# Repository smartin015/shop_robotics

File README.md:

# L2 Workshop Robotics

Firmware and control software for workshop/makerspace robots.

Ensembles of programs are started via the `./launch.sh` script.

# Layout

https://docs.google.com/drawings/d/1Mtd4x5n-zbuuM7uRhCHO-HnwOfN_e4qv0sVR_wNz95c

## Docs

Contains various docs / presentation elements

## Sim

Contains configuration and setup for physical simulation of hardware (typically using Webots).

This is sometimes paired up to real firmware/control software for integration testing.

## Hardware

Contains KiCAD, FreeCAD, SVG and other files for making the physical bits of robots.

## Firmware

Contains code that goes on the robot itself - firmware uses https://platformio.org/ as an environment to allow
for cross-platform builds and native emulation.

## Control

Contains higher-level control software that receives input from the user/environment and sends commands to the firmware.

## Display

Contains programs for displaying the state of the robot and what it sees - on a computer or on embedded screens

# Development

To setup a dev environment, you will need:

* [Docker](https://docs.docker.com/engine/install/ubuntu/)
  * IMPORTANT: [BuildKit](https://docs.docker.com/develop/develop-images/build_enhancements/) must be enabled for simulation builds
* [docker-compose](https://docs.docker.com/compose/install/)
* [This repository](https://github.com/smartin015/shop_robotics)

## Building containers

For the simulation container, you will need to enable BuildKit for docker (see above). You can ignore the warnings about missing environment variables, as they aren't used at build time.

```shell
docker-compose --profile headless --profile webots build
```

For manual/test image builds of the sim container, with more logs:
```
docker buildx build --progress=plain --tag shop_robotics_sim .
```

## Running profiles

```shell
docker-compose --env-file tribot.env -p shop_robotics --profile <webots|gamepad|headless> up
```

**Webots**

This runs a webots simulation of the AR3 robotic arm, with a separate web interface (localhost:8000) and a simulated copy of the firmware which normally lives in the control board of the robot.

Note that with `--stream` supplied in the `webots_sim` container command, you can visit `http://ip:1234/index.html` to see the [streaming server](https://cyberbotics.com/doc/guide/web-streaming) view of the robot simulation.

**Headless**

This runs a "stub" simulator (vastly simplified vs Webots) plus the firmware and web interface. Use this to prototype quickly on the web interface / firmware without having to restart Webots every time.

The `tribot_headless` version runs a 3-joint simulation, to match the omniwheel robot's number of wheels.

**Gamepad**

This runs an additional process that connects to a USB XBox 360 controller and allows for jogging the robot. It's currently hardcoded for 3 axes only,
and must be run along with another environment (e.g. `docker-compose --profile headless --profile gamepad up`)

# Extras

Possibly useful for getting MoveIt! control working: 

- (ROS) https://github.com/ongdexter/ar3_core
- (ROS2) https://github.com/RIF-Robotics/ar3_ros

# Lessons learned

* ZeroMQ: IPC can handle PAIR sockets, but:
  * If multiple users (i.e. firmware & sim containers, since firmware runs as a user and not root) the file must have the correct unix permissions (chmod 777 to be lazy)
  * Socket must remain open on both ends. When it closes, it can't be reopened. This is a property of PAIR sockets.

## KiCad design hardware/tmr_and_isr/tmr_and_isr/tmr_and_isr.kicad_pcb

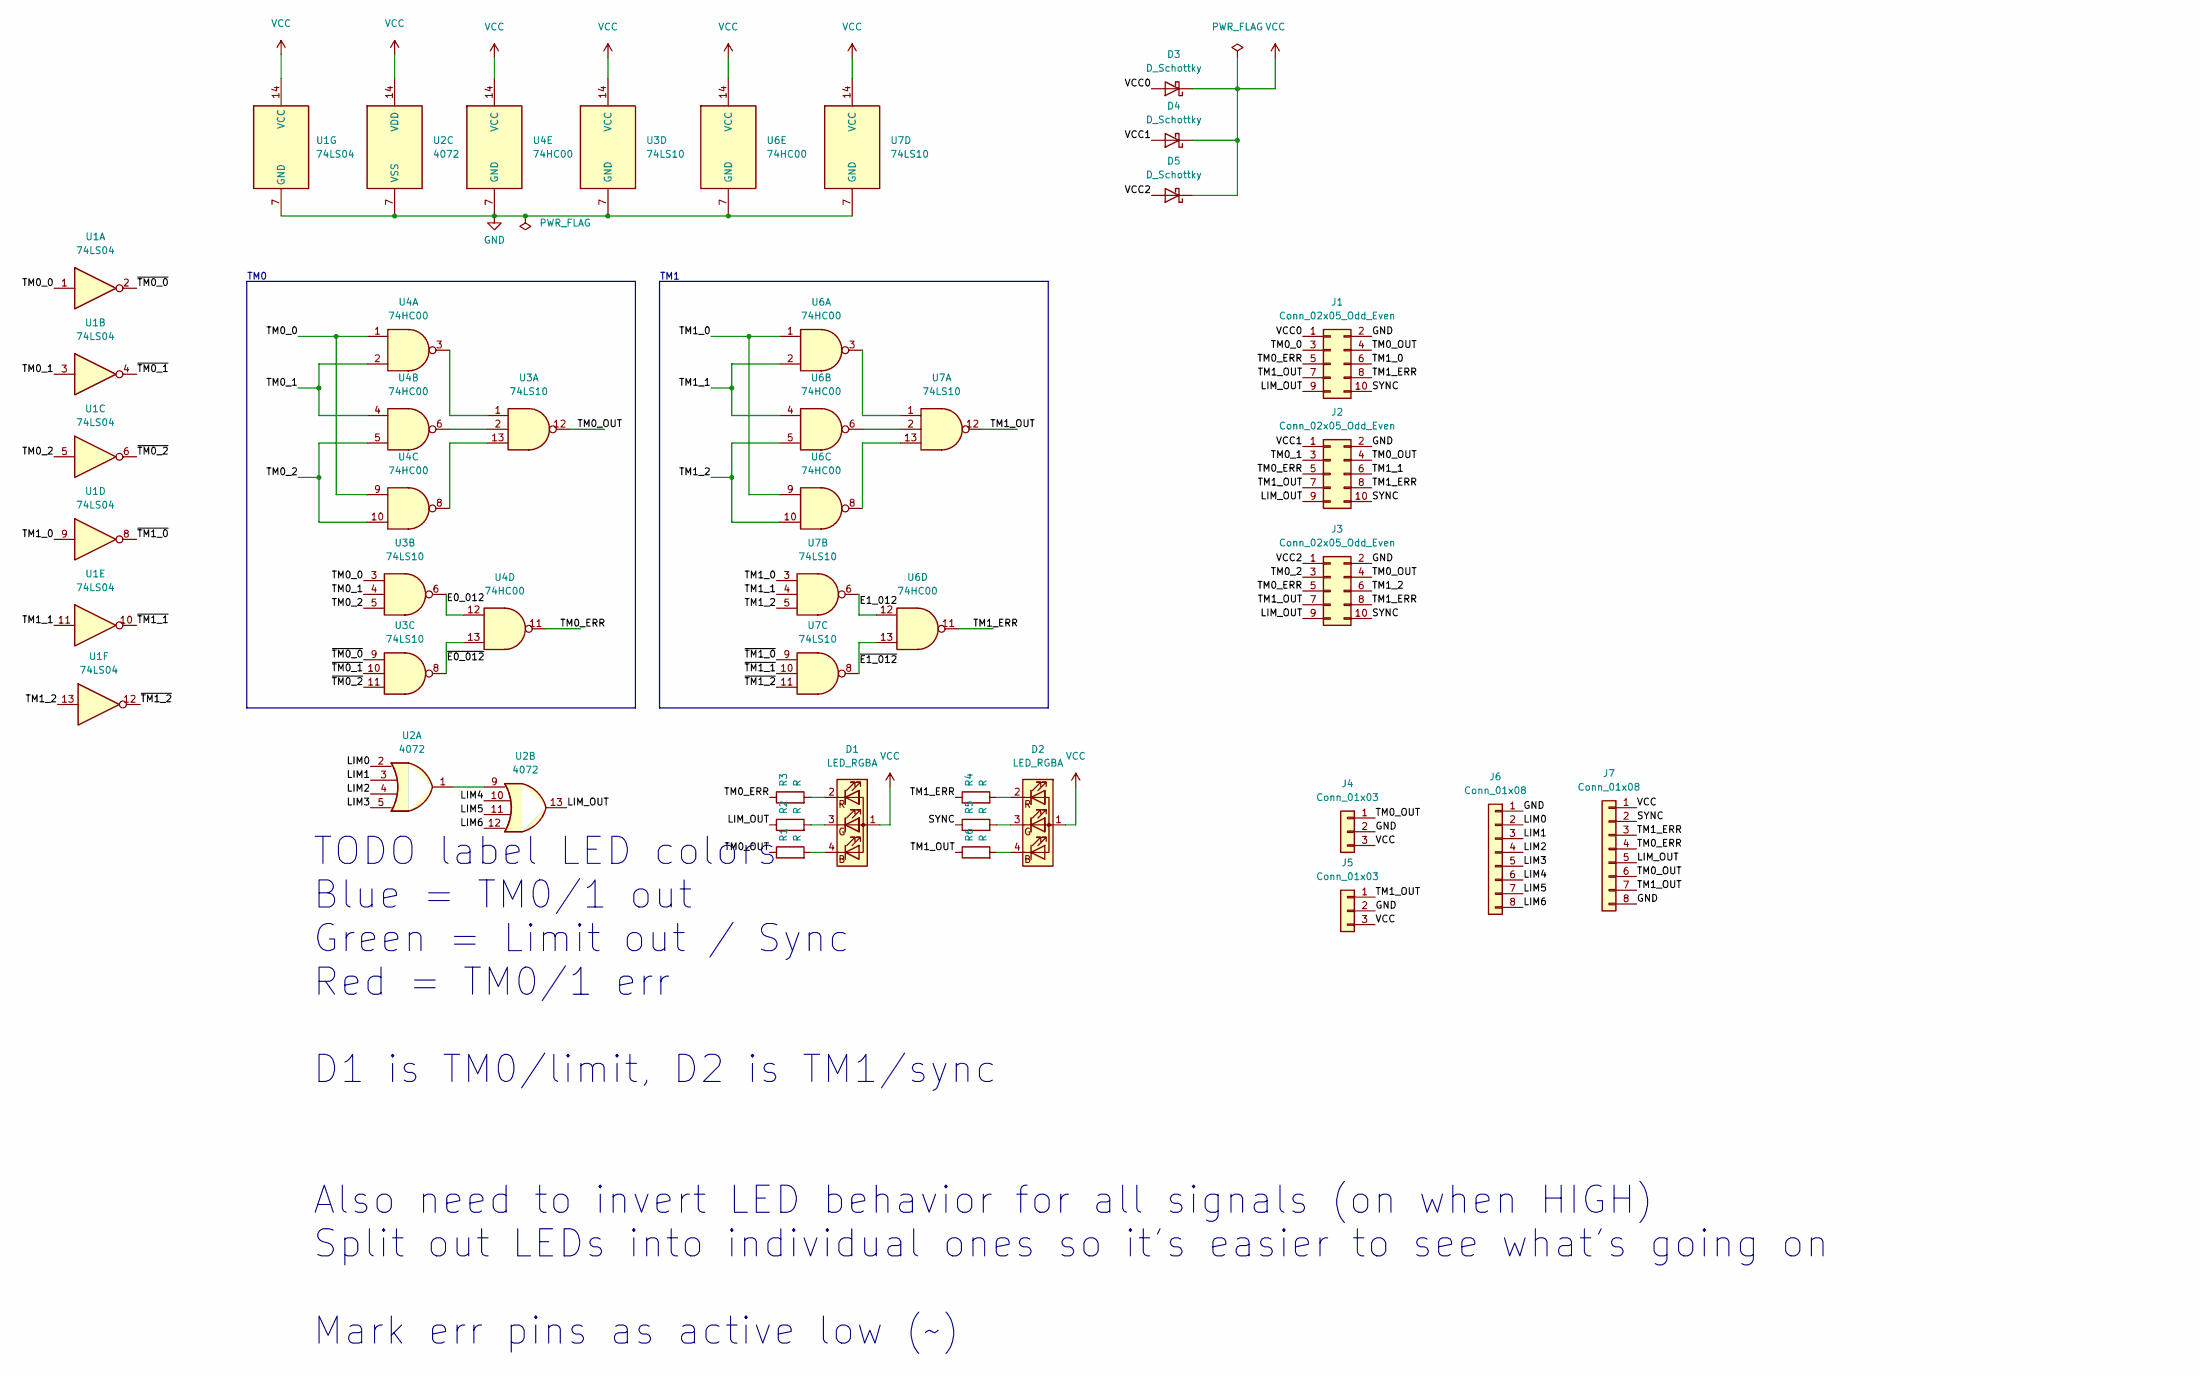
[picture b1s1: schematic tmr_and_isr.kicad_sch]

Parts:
D1, D2: LED_RGBA; LED_RGB_1210
D3, D4, D5: D_Schottky; D_0603_1608Metric
J1, J2, J3: Conn_02x05_Odd_Even; PinSocket_2x05_P2.54mm_Vertical
J4, J5: Conn_01x03; JST_PH_B3B-PH-K_1x03_P2.00mm_Vertical
J6, J7: Conn_01x08; PinHeader_1x08_P2.54mm_Vertical
R1, R2, R3, R4, R5, R6: R; R_0603_1608Metric_Pad0.98x0.95mm_HandSolder
U1: 74LS04; SOIC-14_3.9x8.7mm_P1.27mm
U2: 4072; TSSOP-14_4.4x5mm_P0.65mm
U3, U7: 74LS10; TSSOP-14_4.4x5mm_P0.65mm
U4, U6: 74HC00; SOIC-14_3.9x8.7mm_P1.27mm

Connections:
/LIM0: J6.2, U2.2
/LIM1: J6.3, U2.3
/LIM2: J6.4, U2.4
/LIM3: J6.5, U2.5
/LIM4: J6.6, U2.10
/LIM5: J6.7, U2.11
/LIM6: J6.8, U2.12
/LIM_OUT: J1.9, J2.9, J3.9, J7.5, R2.1, U2.13
/SYNC: J1.10, J2.10, J3.10, J7.2, R5.1
/TM0_0: J1.3, U1.1, U3.3, U4.1, U4.9
/TM0_1: J2.3, U1.3, U3.4, U4.2, U4.4
/TM0_2: J3.3, U1.5, U3.5, U4.5, U4.10
/TM0_ERR: J1.5, J2.5, J3.5, J7.4, R3.1, U4.11
/TM0_OUT: J1.4, J2.4, J3.4, J4.1, J7.6, R1.1, U3.12
/TM1_0: J1.6, U1.9, U6.1, U6.9, U7.3
/TM1_1: J2.6, U1.11, U6.2, U6.4, U7.4
/TM1_2: J3.6, U1.13, U6.5, U6.10, U7.5
/TM1_ERR: J1.8, J2.8, J3.8, J7.3, R4.1, U6.11
/TM1_OUT: J1.7, J2.7, J3.7, J5.1, J7.7, R6.1, U7.12
/VCC0: D3.2 (A), J1.1
/VCC1: D4.2 (A), J2.1
/VCC2: D5.2 (A), J3.1
/~TM0_0: U1.2, U3.9
/~TM0_1: U1.4, U3.10
/~TM0_2: U1.6, U3.11
/~TM1_0: U1.8, U7.9
/~TM1_1: U1.10, U7.10
/~TM1_2: U1.12, U7.11
GND: J1.2, J2.2, J3.2, J4.2, J5.2, J6.1, J7.8, U1.7 (GND), U2.7 (VSS), U3.7 (GND), U4.7 (GND), U6.7 (GND), U7.7 (GND)
unnamed: D1.2 (RK), R3.2
unnamed: D1.3 (GK), R2.2
unnamed: D1.4 (BK), R1.2
unnamed: D2.2 (RK), R4.2
unnamed: D2.3 (GK), R5.2
unnamed: D2.4 (BK), R6.2
unnamed: U2.1, U2.9
unnamed: U3.1, U4.3
unnamed: U3.2, U4.6
unnamed: U3.6, U4.12
unnamed: U3.8, U4.13
unnamed: U3.13, U4.8
unnamed: U6.3, U7.1
unnamed: U6.6, U7.2
unnamed: U6.8, U7.13
unnamed: U6.12, U7.6
unnamed: U6.13, U7.8
VCC: D1.1 (A), D2.1 (A), D3.1 (K), D4.1 (K), D5.1 (K), J4.3, J5.3, J7.1, U1.14 (VCC), U2.14 (VDD), U3.14 (VCC), U4.14 (VCC), U6.14 (VCC), U7.14 (VCC)

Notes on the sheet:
TODO label LED colors Blue = TM0/1 out Green = Limit out / Sync Red = TM0/1 err D1 is TM0/limit, D2 is TM1/sync Also need to invert LED behavior for all signals (on when HIGH) Split out LEDs into individual ones so it's easier to see what's going on Mark err pins as active low (~)
TM1
TM0

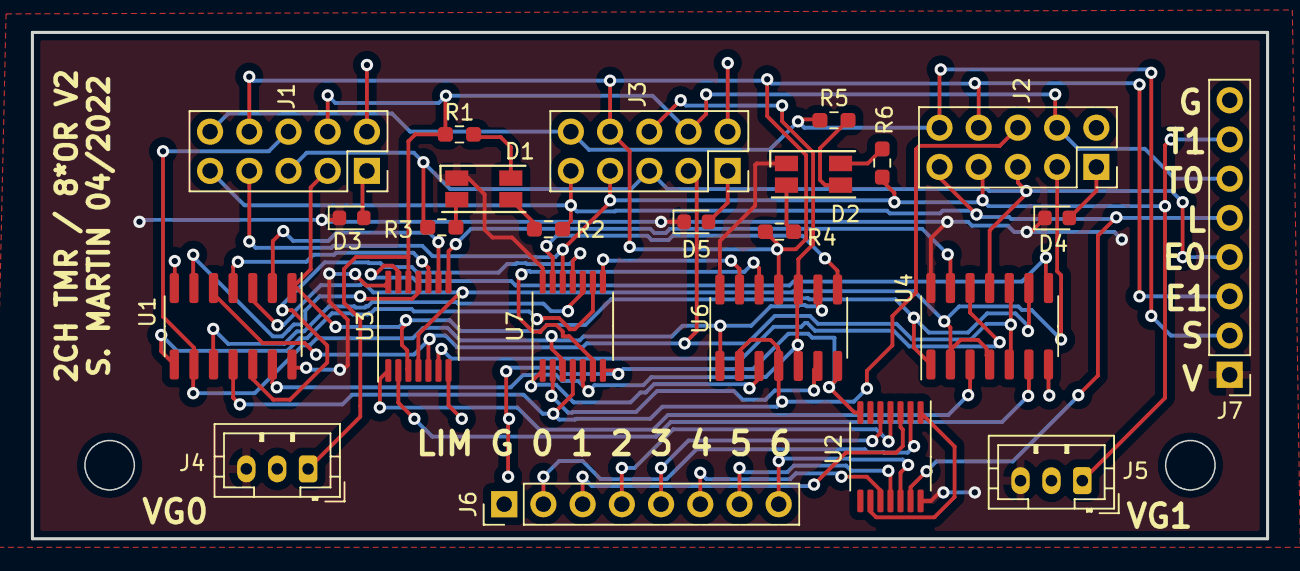
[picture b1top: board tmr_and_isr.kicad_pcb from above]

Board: 2 copper layers, 80.0 x 32.8 mm, 24 parts (0 on the bottom side), 47 nets.

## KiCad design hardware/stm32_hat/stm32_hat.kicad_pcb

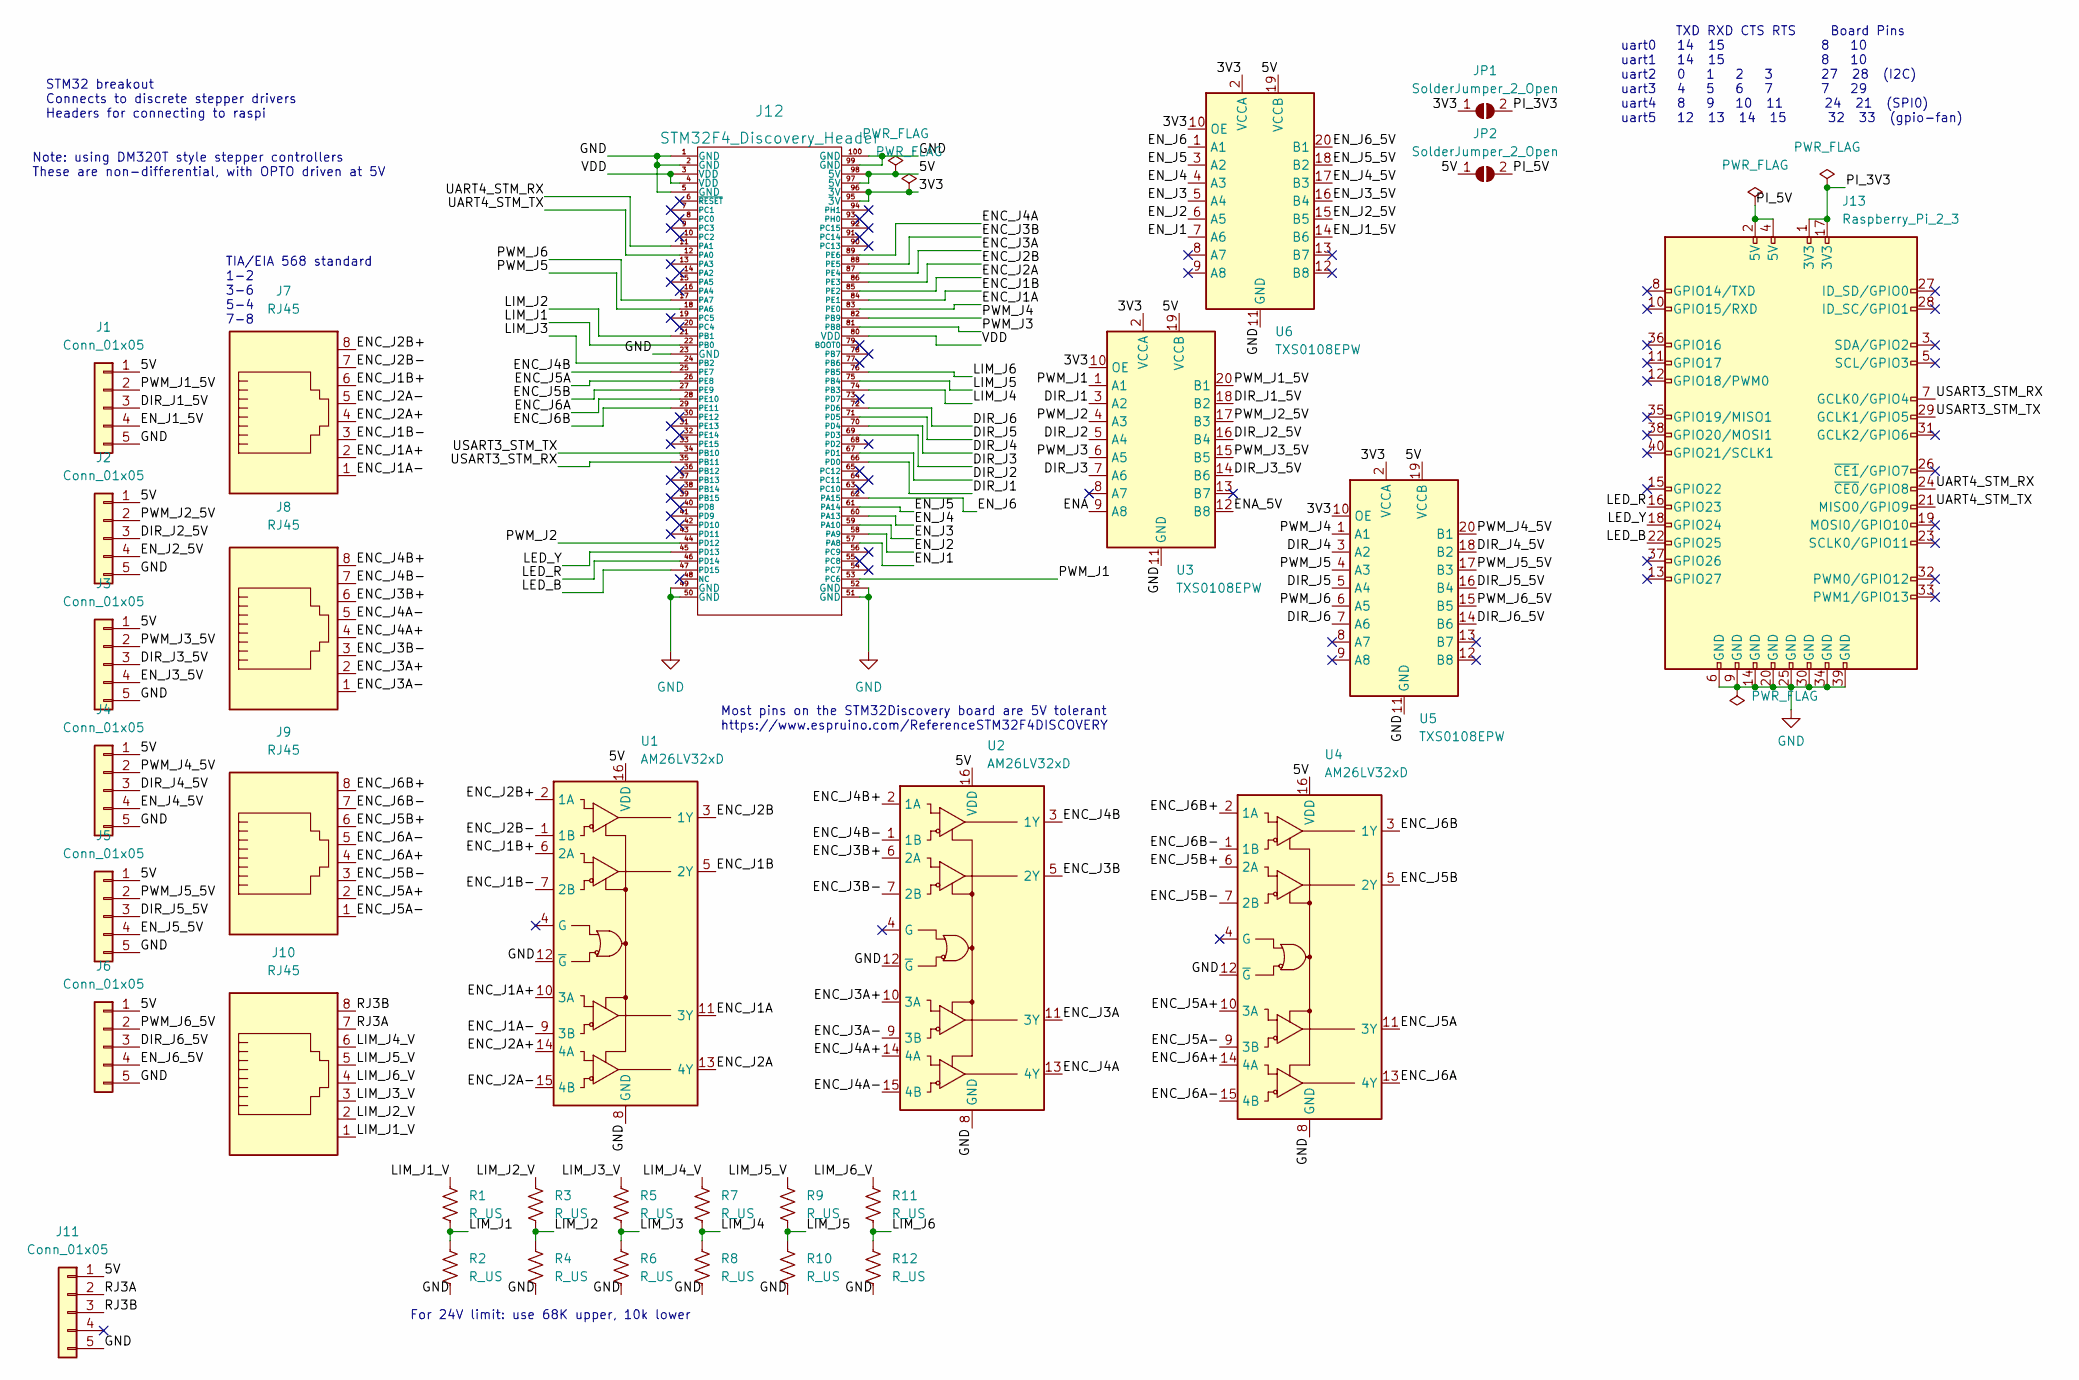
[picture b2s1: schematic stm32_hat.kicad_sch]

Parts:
J1, J2, J3, J4, J5, J6, J11: Conn_01x05; JST_PH_B5B-PH-K_1x05_P2.00mm_Vertical
J7, J8, J9, J10: RJ45; RJ45_Amphenol_54602-x08_Horizontal
J12: STM32F4_Discovery_Header; stm32f4_discovery_header
J13: Raspberry_Pi_2_3; PinHeader_2x20_P2.54mm_Vertical
JP1, JP2: SolderJumper_2_Open; SolderJumper-2_P1.3mm_Open_Pad1.0x1.5mm
R1, R2, R3, R4, R5, R6, R7, R8, R9, R10, R11, R12: R_US; R_0603_1608Metric_Pad0.98x0.95mm_HandSolder
U1, U2, U4: AM26LV32xD; SOIC-16_3.9x9.9mm_P1.27mm
U3, U5, U6: TXS0108EPW; TSSOP-20_4.4x6.5mm_P0.65mm

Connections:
/3V3: J12.95 (3V), J12.96 (3V), JP1.1 (A), U3.2 (VCCA), U3.10 (OE), U5.2 (VCCA), U5.10 (OE), U6.2 (VCCA), U6.10 (OE)
/5V: J1.1, J2.1, J3.1, J4.1, J5.1, J6.1, J11.1, J12.97 (5V), J12.98 (5V), JP2.1 (A), U1.16 (VDD), U2.16 (VDD), U3.19 (VCCB), U4.16 (VDD), U5.19 (VCCB), U6.19 (VCCB)
/DIR_J1: J12.66 (PD0), U3.3 (A2)
/DIR_J1_5V: J1.3, U3.18 (B2)
/DIR_J2: J12.67 (PD1), U3.5 (A4)
/DIR_J2_5V: J2.3, U3.16 (B4)
/DIR_J3: J12.69 (PD3), U3.7 (A6)
/DIR_J3_5V: J3.3, U3.14 (B6)
/DIR_J4: J12.70 (PD4), U5.3 (A2)
/DIR_J4_5V: J4.3, U5.18 (B2)
/DIR_J5: J12.71 (PD5), U5.5 (A4)
/DIR_J5_5V: J5.3, U5.16 (B4)
/DIR_J6: J12.72 (PD6), U5.7 (A6)
/DIR_J6_5V: J6.3, U5.14 (B6)
/ENA: U3.9 (A8)
/ENA_5V: U3.12 (B8)
/ENC_J1A: J12.83 (PE0), U1.11 (3Y)
/ENC_J1A+: J7.2, U1.10 (3A)
/ENC_J1A-: J7.1, U1.9 (3B)
/ENC_J1B: J12.84 (PE1), U1.5 (2Y)
/ENC_J1B+: J7.6, U1.6 (2A)
/ENC_J1B-: J7.3, U1.7 (2B)
/ENC_J2A: J12.85 (PE2), U1.13 (4Y)
/ENC_J2A+: J7.4, U1.14 (4A)
/ENC_J2A-: J7.5, U1.15 (4B)
/ENC_J2B: J12.86 (PE3), U1.3 (1Y)
/ENC_J2B+: J7.8, U1.2 (1A)
/ENC_J2B-: J7.7, U1.1 (1B)
/ENC_J3A: J12.87 (PE4), U2.11 (3Y)
/ENC_J3A+: J8.2, U2.10 (3A)
/ENC_J3A-: J8.1, U2.9 (3B)
/ENC_J3B: J12.88 (PE5), U2.5 (2Y)
/ENC_J3B+: J8.6, U2.6 (2A)
/ENC_J3B-: J8.3, U2.7 (2B)
/ENC_J4A: J12.89 (PE6), U2.13 (4Y)
/ENC_J4A+: J8.4, U2.14 (4A)
/ENC_J4A-: J8.5, U2.15 (4B)
/ENC_J4B: J12.25 (PE7), U2.3 (1Y)
/ENC_J4B+: J8.8, U2.2 (1A)
/ENC_J4B-: J8.7, U2.1 (1B)
/ENC_J5A: J12.26 (PE8), U4.11 (3Y)
/ENC_J5A+: J9.2, U4.10 (3A)
/ENC_J5A-: J9.1, U4.9 (3B)
/ENC_J5B: J12.27 (PE9), U4.5 (2Y)
/ENC_J5B+: J9.6, U4.6 (2A)
/ENC_J5B-: J9.3, U4.7 (2B)
/ENC_J6A: J12.28 (PE10), U4.13 (4Y)
/ENC_J6A+: J9.4, U4.14 (4A)
/ENC_J6A-: J9.5, U4.15 (4B)
/ENC_J6B: J12.29 (PE11), U4.3 (1Y)
/ENC_J6B+: J9.8, U4.2 (1A)
/ENC_J6B-: J9.7, U4.1 (1B)
/EN_J1: J12.57 (PA8), U6.7 (A6)
/EN_J1_5V: J1.4, U6.14 (B6)
/EN_J2: J12.58 (PA9), U6.6 (A5)
/EN_J2_5V: J2.4, U6.15 (B5)
/EN_J3: J12.59 (PA10), U6.5 (A4)
/EN_J3_5V: J3.4, U6.16 (B4)
/EN_J4: J12.60 (PA13), U6.4 (A3)
/EN_J4_5V: J4.4, U6.17 (B3)
/EN_J5: J12.61 (PA14), U6.3 (A2)
/EN_J5_5V: J5.4, U6.18 (B2)
/EN_J6: J12.62 (PA15), U6.1 (A1)
/EN_J6_5V: J6.4, U6.20 (B1)
/LED_B: J12.47 (PD15), J13.22 (GPIO25)
/LED_R: J12.46 (PD14), J13.16 (GPIO23)
/LED_Y: J12.45 (PD13), J13.18 (GPIO24)
/LIM_J1: J12.22 (PB0), R1.2, R2.1
/LIM_J1_V: J10.1, R1.1
/LIM_J2: J12.21 (PB1), R3.2, R4.1
/LIM_J2_V: J10.2, R3.1
/LIM_J3: J12.24 (PB2), R5.2, R6.1
/LIM_J3_V: J10.3, R5.1
/LIM_J4: J12.74 (PB3), R7.2, R8.1
/LIM_J4_V: J10.6, R7.1
/LIM_J5: J12.75 (PB4), R9.2, R10.1
/LIM_J5_V: J10.5, R9.1
/LIM_J6: J12.76 (PB5), R11.2, R12.1
/LIM_J6_V: J10.4, R11.1
/PI_3V3: J13.1 (3V3), J13.17 (3V3), JP1.2 (B)
/PI_5V: J13.2 (5V), J13.4 (5V), JP2.2 (B)
/PWM_J1: J12.53 (PC6), U3.1 (A1)
/PWM_J1_5V: J1.2, U3.20 (B1)
/PWM_J2: J12.44 (PD12), U3.4 (A3)
/PWM_J2_5V: J2.2, U3.17 (B3)
/PWM_J3: J12.81 (PB8), U3.6 (A5)
/PWM_J3_5V: J3.2, U3.15 (B5)
/PWM_J4: J12.82 (PB9), U5.1 (A1)
/PWM_J4_5V: J4.2, U5.20 (B1)
/PWM_J5: J12.18 (PA6), U5.4 (A3)
/PWM_J5_5V: J5.2, U5.17 (B3)
/PWM_J6: J12.17 (PA7), U5.6 (A5)
/PWM_J6_5V: J6.2, U5.15 (B5)
/RJ3A: J10.7, J11.2
/RJ3B: J10.8, J11.3
/UART4_STM_RX: J12.11 (PA1), J13.24 (~CE0/GPIO8)
/UART4_STM_TX: J12.12 (PA0), J13.21 (MISO0/GPIO9)
/USART3_STM_RX: J12.35 (PB11), J13.7 (GCLK0/GPIO4)
/USART3_STM_TX: J12.34 (PB10), J13.29 (GCLK1/GPIO5)
/VDD: J12.3 (VDD), J12.4 (VDD), J12.80 (VDD)
GND: J1.5, J2.5, J3.5, J4.5, J5.5, J6.5, J11.5, J12.1 (GND), J12.2 (GND), J12.5 (GND), J12.23 (GND), J12.49 (GND), J12.50 (GND), J12.51 (GND), J12.52 (GND), J12.99 (GND), J12.100 (GND), J13.6 (GND), J13.9 (GND), J13.14 (GND), J13.20 (GND), J13.25 (GND), J13.30 (GND), J13.34 (GND), J13.39 (GND), R2.2, R4.2, R6.2, R8.2, R10.2, R12.2, U1.8 (GND), U1.12 (~G), U2.8 (GND), U2.12 (~G), U3.11 (GND), U4.8 (GND), U4.12 (~G), U5.11 (GND), U6.11 (GND)

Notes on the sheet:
Most pins on the STM32Discovery board are 5V tolerant https://www.espruino.com/ReferenceSTM32F4DISCOVERY
STM32 breakout Connects to discrete stepper drivers Headers for connecting to raspi
Note: using DM320T style stepper controllers These are non-differential, with OPTO driven at 5V
For 24V limit: use 68K upper, 10k lower
TXD RXD CTS RTS Board Pins uart0 14 15 8 10 uart1 14 15 8 10 uart2 0 1 2 3 27 28 (I2C) uart3 4 5 6 7 7 29 uart4 8 9 10 11 24 21 (SPI0) uart5 12 13 14 15 32 33 (gpio-fan)
TIA/EIA 568 standard 1-2 3-6 5-4 7-8

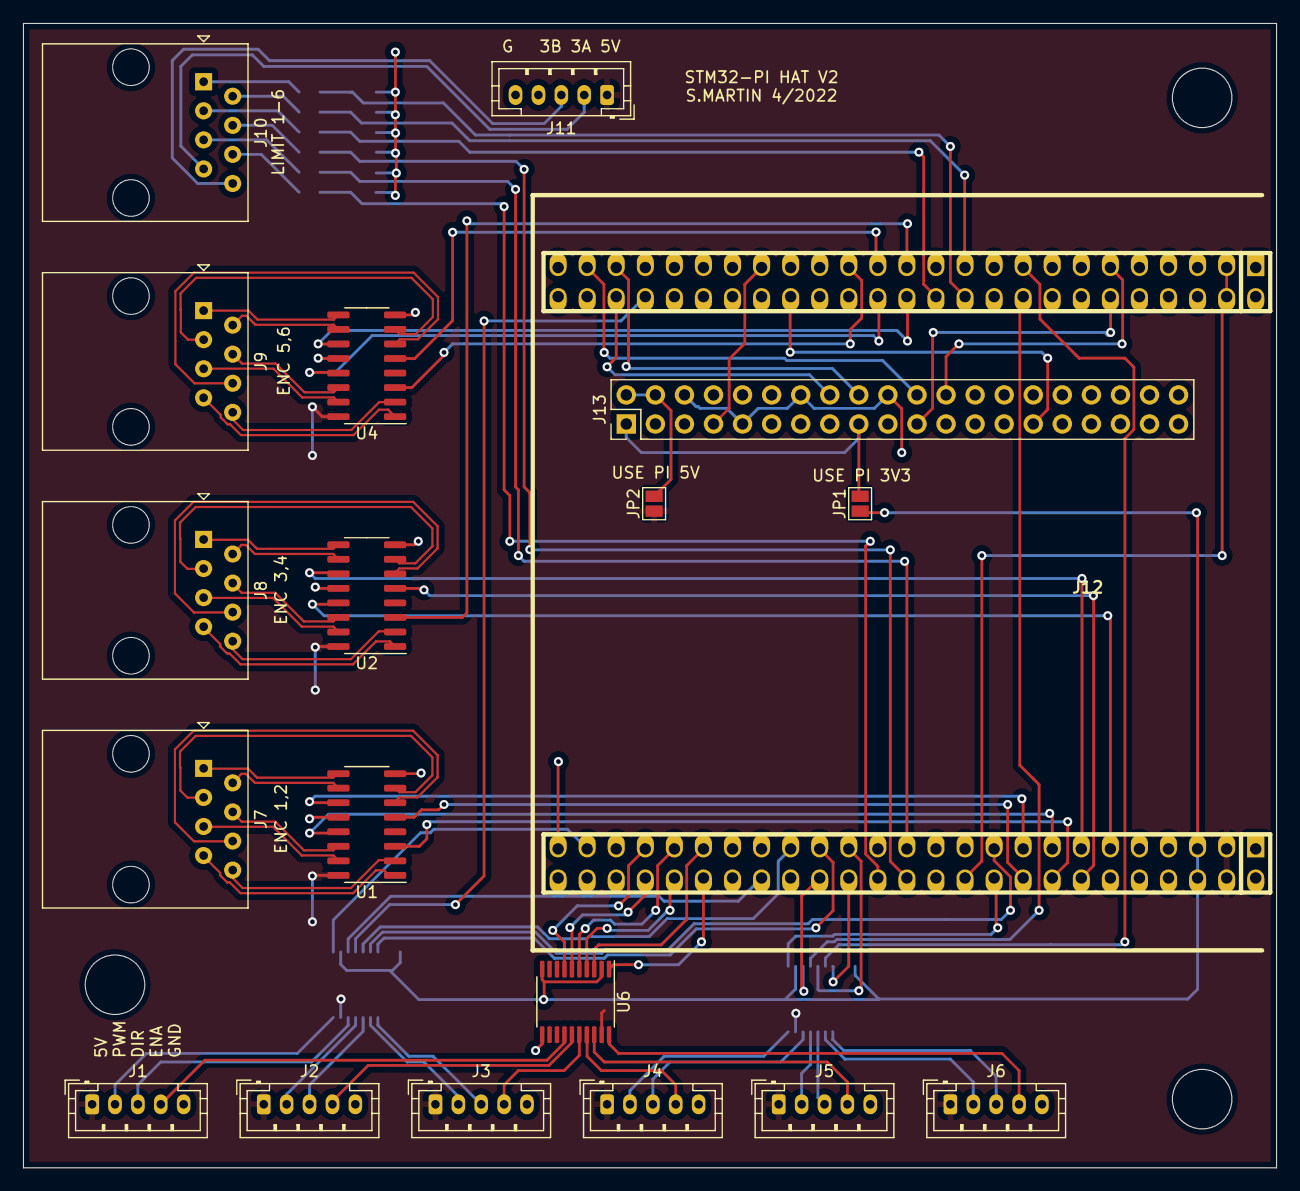
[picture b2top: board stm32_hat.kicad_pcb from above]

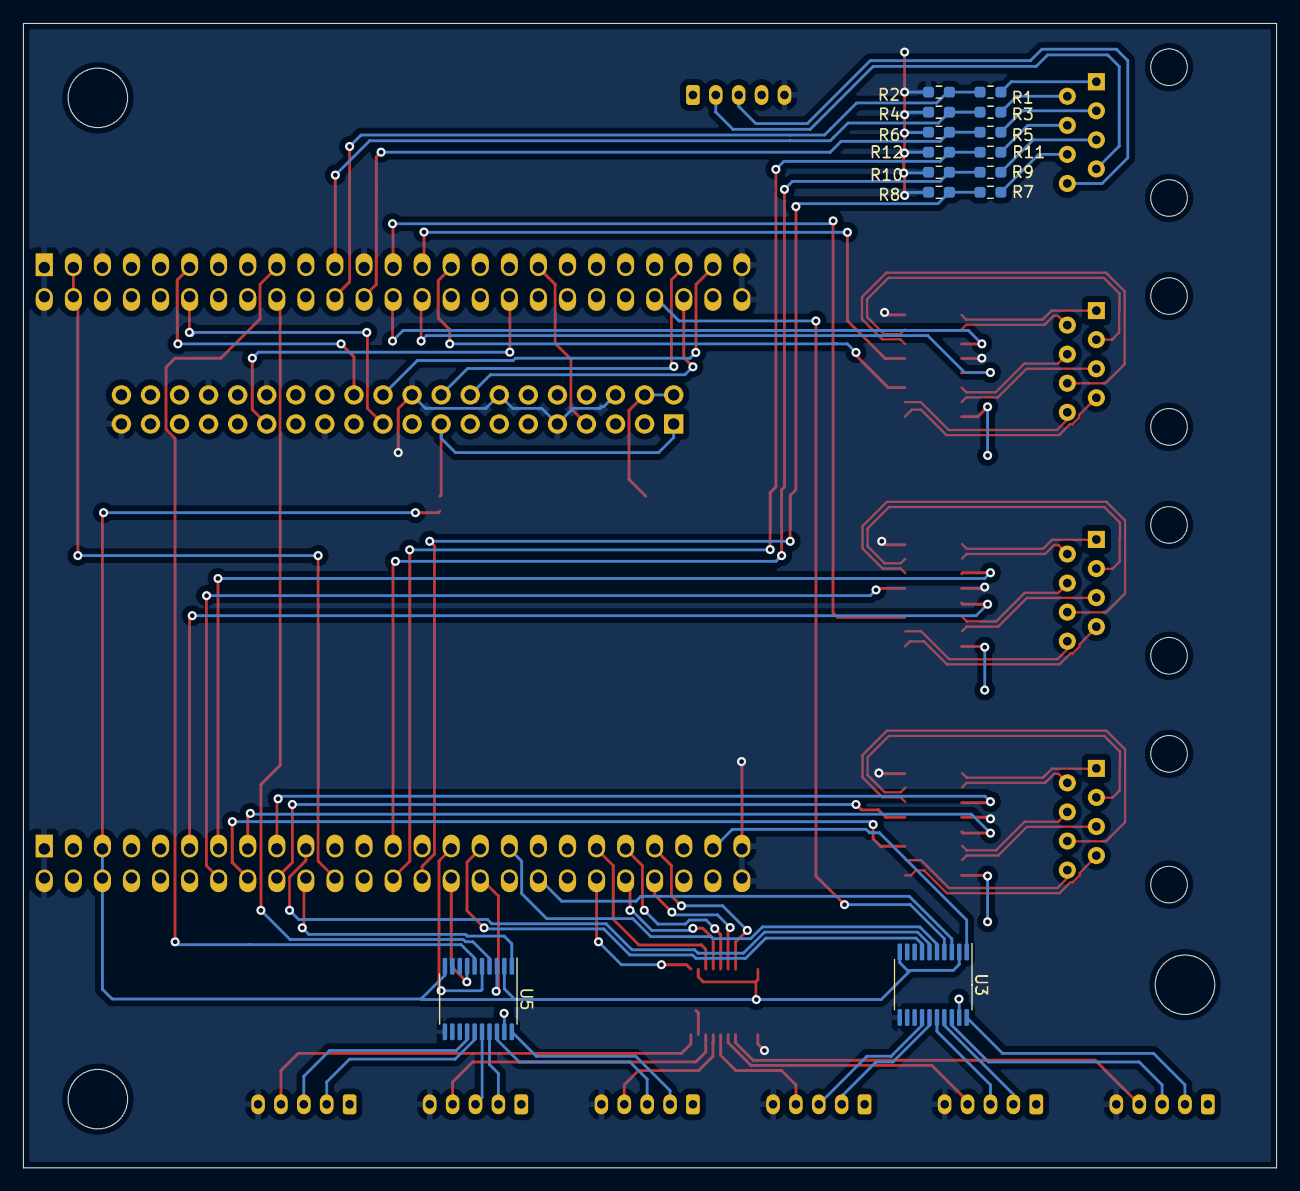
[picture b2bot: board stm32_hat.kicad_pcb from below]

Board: 2 copper layers, 109.5 x 100.0 mm, 33 parts (14 on the bottom side), 99 nets.

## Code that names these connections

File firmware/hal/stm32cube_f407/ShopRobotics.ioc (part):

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PD12.GPIO_Label=PWM_J2
PE11.GPIOParameters=GPIO_Label,GPIO_ModeDefaultEXTI
PB10.Mode=Asynchronous
PA14.GPIO_Label=EN_J5
PD3.GPIOParameters=GPIO_Label
PC6.GPIO_Label=PWM_J1
PA6.GPIO_Label=PWM_J5
PD6.GPIO_Label=DIR_J6
PE6.GPIO_Label=ENC_J4A
RCC.SYSCLKSource=RCC_SYSCLKSOURCE_PLLCLK
PD15.GPIOParameters=GPIO_PuPd,GPIO_Label
PD4.Signal=GPIO_Output
PD0.Signal=GPIO_Output
PE5.Signal=GPXTI5
PE1.Signal=GPXTI1
PB2.Signal=GPIO_Input
PD1.GPIOParameters=GPIO_Label
PD1.GPIO_Label=DIR_J2
PE8.GPIO_ModeDefaultEXTI=GPIO_MODE_IT_RISING_FALLING
PB0.GPIOParameters=GPIO_Label
PE0.GPIOParameters=GPIO_Label
PE9.Signal=GPXTI9
PB1.GPIO_Label=LIM_J2
PE4.GPIO_Label=ENC_J3A
PE2.Signal=GPXTI2
PD14.GPIO_PuPd=GPIO_PULLUP
PA8.Signal=GPIO_Output
PE10.Signal=GPXTI10
Mcu.Package=LQFP100
PB9.Signal=S_TIM11_CH1
PB1.Signal=GPIO_Input
PE10.GPIOParameters=GPIO_Label,GPIO_ModeDefaultEXTI
PD12.Signal=S_TIM4_CH1
PD5.GPIOParameters=GPIO_Label
PA10.Signal=GPIO_Output
PB9.GPIO_PuPd=GPIO_PULLUP
PC6.GPIO_PuPd=GPIO_PULLUP
PA6.GPIO_Speed=GPIO_SPEED_FREQ_HIGH
PE10.GPIO_Label=ENC_J6A
PC6.GPIO_Speed=GPIO_SPEED_FREQ_HIGH
PD15.Signal=GPIO_Output
PA6.GPIOParameters=GPIO_Speed,GPIO_PuPd,GPIO_Label
PD6.GPIOParameters=GPIO_Label
PA15.GPIOParameters=GPIO_Label
PA9.GPIO_Label=EN_J2
PD3.Signal=GPIO_Output
PB8.GPIO_PuPd=GPIO_PULLUP
PC6.Signal=S_TIM3_CH1
PD13.GPIOParameters=GPIO_PuPd,GPIO_Label
PD1.Signal=GPIO_Output
PA0-WKUP.Signal=UART4_TX
PA0-WKUP.Mode=Asynchronous
PB8.GPIO_Label=PWM_J3
PE10.GPIO_ModeDefaultEXTI=GPIO_MODE_IT_RISING_FALLING
PA8.GPIO_Label=EN_J1
PB11.Mode=Asynchronous
PE8.GPIO_Label=ENC_J5A
PA9.Signal=GPIO_Output
PE9.GPIO_Label=ENC_J5B
PB10.Signal=USART3_TX
PE1.GPIO_Label=ENC_J1B
PA7.GPIO_Speed=GPIO_SPEED_FREQ_HIGH
PA1.Mode=Asynchronous
PB4.GPIO_Label=LIM_J5
PE8.Signal=GPXTI8
PD14.GPIOParameters=GPIO_PuPd,GPIO_Label
PB5.Signal=GPIO_Input
PA14.GPIOParameters=GPIO_Label
PE5.GPIO_Label=ENC_J3B
PD0.GPIOParameters=GPIO_Label
PE3.Signal=GPXTI3
PE9.GPIO_ModeDefaultEXTI=GPIO_MODE_IT_RISING_FALLING
PB0.Signal=GPIO_Input
PA7.GPIOParameters=GPIO_Speed,GPIO_PuPd,GPIO_Label
Mcu.UserName=STM32F407VGTx
PE11.GPIO_Label=ENC_J6B
PA9.GPIOParameters=GPIO_Label
PD0.GPIO_Label=DIR_J1
PB0.GPIO_Label=LIM_J1
PB11.Signal=USART3_RX
PE5.GPIOParameters=GPIO_Label
PB5.GPIOParameters=GPIO_Label
PD13.Signal=GPIO_Output
PA15.GPIO_Label=EN_J6
PB4.GPIOParameters=GPIO_Label
PE4.GPIOParameters=GPIO_Label
PA8.GPIOParameters=GPIO_Label
RCC.HSE_VALUE=25000000
PA6.GPIO_PuPd=GPIO_PULLUP
PA10.GPIO_Label=EN_J3
PE3.GPIOParameters=GPIO_Label
PB3.GPIOParameters=GPIO_Label
PE4.Signal=GPXTI4
PE6.GPIOParameters=GPIO_Label
PA13.GPIOParameters=GPIO_Label
PD13.GPIO_Label=YELLOW_LED
PA6.Signal=S_TIM13_CH1
PD5.GPIO_Label=DIR_J5
PD15.GPIO_PuPd=GPIO_PULLUP
PA15.Signal=GPIO_Output
PE0.GPIO_Label=ENC_J1A
PB9.GPIO_Speed=GPIO_SPEED_FREQ_HIGH
PB5.GPIO_Label=LIM_J6
PD3.GPIO_Label=DIR_J3
PE7.Signal=GPXTI7
PD6.Signal=GPIO_Output
PE2.GPIO_Label=ENC_J2A
PB4.Signal=GPIO_Input
PB3.GPIO_Label=LIM_J4
PE8.GPIOParameters=GPIO_Label,GPIO_ModeDefaultEXTI
PD12.GPIO_Speed=GPIO_SPEED_FREQ_HIGH
PD15.GPIO_Label=BLUE_LED
PB8.GPIOParameters=GPIO_Speed,GPIO_PuPd,GPIO_Label
PB9.GPIO_Label=PWM_J4
PD5.Signal=GPIO_Output
PE9.GPIOParameters=GPIO_Label,GPIO_ModeDefaultEXTI
PB9.GPIOParameters=GPIO_Speed,GPIO_PuPd,GPIO_Label
PA13.Signal=GPIO_Output
PE11.GPIO_ModeDefaultEXTI=GPIO_MODE_IT_RISING_FALLING
PD12.GPIOParameters=GPIO_Speed,GPIO_PuPd,GPIO_Label
PE7.GPIOParameters=GPIO_Label,GPIO_ModeDefaultEXTI
PB2.GPIOParameters=GPIO_Label
PE2.GPIOParameters=GPIO_Label
PE11.Signal=GPXTI11
PA7.GPIO_PuPd=GPIO_PULLUP
PA1.Signal=UART4_RX
board=custom
PD4.GPIO_Label=DIR_J4
PD4.GPIOParameters=GPIO_Label
PA10.GPIOParameters=GPIO_Label
PE7.GPIO_ModeDefaultEXTI=GPIO_MODE_IT_RISING_FALLING
PD13.GPIO_PuPd=GPIO_PULLUP
PD14.GPIO_Label=RED_LED
PE6.Signal=GPXTI6
Mcu.Name=STM32F407V(E-G)Tx
PE0.Signal=GPXTI0
PE7.GPIO_Label=ENC_J4B
PA13.GPIO_Label=EN_J4
PD14.Signal=GPIO_Output
PB3.Signal=GPIO_Input
RCC.SYSCLKFreq_VALUE=168000000
PA7.GPIO_Label=PWM_J6
PA14.Signal=GPIO_Output
PB2.GPIO_Label=LIM_J3
PC6.GPIOParameters=GPIO_Speed,GPIO_PuPd,GPIO_Label
PB8.Signal=S_TIM10_CH1
PE3.GPIO_Label=ENC_J2B
PB8.GPIO_Speed=GPIO_SPEED_FREQ_HIGH
PD12.GPIO_PuPd=GPIO_PULLUP
PE1.GPIOParameters=GPIO_Label
PB1.GPIOParameters=GPIO_Label
PA7.Signal=S_TIM14_CH1

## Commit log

2022-01-13 Merged launch scripts, fleshed out readme
2022-01-13 All containers build, docker-compose config cleaned up, still runtime errors
2022-01-14 Removed unnecessary ros2 nodes, got native simulation working again
2022-01-14 Added prospective repos for further development
2022-01-26 Small fixes, more documentation
2022-02-02 Deduplicated firmware includes in hal/
2022-02-04 Improved firmware coupling via IPC to simulator
2022-02-15 add missing folder
2022-02-15 Enable web streaming on webots
2022-02-19 Refactor UI to split out joint graphs, standardize config passing via environment variable for each container, and set up the start of passing encoder values back to the UI
2022-02-24 Added battery mount stl notebook, refactored web UI and allowed for encoder value passing
2022-02-25 Further web UI changes - individual joint masks etc
2022-02-28 Initial refactor to use motion curves- still need to shake out bugs and write tests
2022-02-28 Switch to status_t based validation of curve intents, adjusted test_curves.py to provide continuous curves. Validation now working
2022-03-01 Optimistic commit for STM32 firmware- builds but likely not runs
2022-03-02 Added LED light indicators to STM32 board, plus readme details
2022-03-02 Add STM32 ioc file for pin mapping of stm32f407
2022-03-07 PWM timers now confirmed to work on stm32 discovery board
2022-03-08 Added stm32pio repo and updated platformio.ini
2022-03-08 Converted whole project to C, as stm32pio only generates C main files
2022-03-08 Add test_uart3
2022-03-09 Native and stm32 now working after switch to czmq library and C files
2022-03-09 Remove not-working prior attempt at STM32 firmware
2022-03-09 Added encoder & limit switch reading in STM32 firmware
2022-03-10 Added curve generator ipynb and curvegen.py ruckig translator
2022-03-10 Added curvegen and curve_generator.ipynb
2022-03-11 Added triple module redundancy kicad project
2022-03-24 Housekeeping, plus improvements to curve generator code
2022-03-24 Add ROS topic communication across docker containers
2022-03-25 Get headless docker-compose working again with native firmware - swapped REQ and REP sockets on sim-firmware comms
2022-04-28 Added STM32Hat PCB (V2)
2022-04-28 Added updated TMR and ISR PCB
2022-04-30 Update tmr/isr circuit with TODOs, add tribot webots env vars and auto-switching between webots worlds
